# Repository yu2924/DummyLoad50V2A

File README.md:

# Dummy Load 50V2A

ハードウェアプロジェクト**Dummy Load 50V2A**のデザインについてまとめます。

## 1. 概要

**Dummy Load 50V2A**は電源回路の負荷テストなどに便利な、定電流電子負荷装置です。
AVRマイコンを使用して電圧・電流・温度をモニタします。

* 最大定格DC50V、2A、50W程度
* 電圧モニタ分解能: 0.1V
* 電流モニタ分解能: 1mA
* 温度モニタ分解能: 1℃
* 電源: DC9～12V 100mA程度
* 動作中の電圧・電流・温度をモニタしながら、負荷電流をコース・ファインの2つのツマミで設定
* 負荷のON/OFFスイッチ

## 2. ツールとマテリアル

**ソフトウェアツール**
* 回路作図: [BSch3V](https://www.suigyodo.com/online/schsoft.htm) 0.83.05
* PCB設計: [KiCad](https://www.kicad.org/) 5.1
* ファームウェア開発: Atmel Studio 7 ([Microchip Studio 7](https://www.microchip.com/en-us/tools-resources/develop/microchip-studio))
* I2Cライブラリ: USI_TWI_Master ([TinyWireM](https://github.com/adafruit/TinyWireM))
* その他作図: [Inkscape](https://inkscape.org/) 1.1

**ハードウェアツール**
* AVRプログラマ: Atmel AVRISP mkIIまたは同等品
* 電圧計・電流計: 電圧と電流の読み取り値の比較基準に信頼できるものが必要です。とりあえず3 1/2桁のDMMでOKです。

**その他**
* ハンダとハンダゴテ、ニッパーとラジオペンチ、ヤスリ、タップとタップハンドル、等々
* スペーサー、ネジ、ワッシャー、アルミ板、等々

**※AVR開発環境のアップデート**
2022-05-31現在、AVRISP mkIIが既にディスコンということもあり、[MPLAB X IDE](https://www.microchip.com/en-us/tools-resources/develop/mplab-x-ide)と[MPLAB SNAP](https://www.microchip.com/en-us/development-tool/PG164100)への移行が良さそうです。Atmel Studioと同じ[Atmel AVR GNU Toolchain](https://www.microchip.com/en-us/tools-resources/develop/microchip-studio/gcc-compilers)も利用できるようです。

## 3. 回路の略解

[回路図](media/DummyLoad50V2A.pdf)

部品は概ね[秋月電子通商](https://akizukidenshi.com/)で購入できるものを中心に選んでいます。

**電子負荷**
オペアンプとMOSFETを使った電流シンクです。
オペアンプは単電源動作で0V入力できるものから広く選べますが、低オフセットのものが望ましいです。
MOSFETも特定の型番に限らず、定格電圧・電流、許容損失、熱抵抗、Vth(on)などの条件に見合ったものの中から広く選べると思います。

コース・ファインの2つのツマミで制御電圧を合成し、負荷電流を設定します。
回路図中480k～∞としている抵抗はオペアンプのオフセットを相殺するためのオプションであり、設定電流を0mAまで絞り込めない場合に追加します。

:bulb:このデザインは定電流負荷ですが、別のアイデアとして基準電圧をターゲット端子から取れば負荷電流が電圧に比例するオーム負荷となります。

**モニタ**
0～50Vの範囲を0.1Vの分解能で表示、オフセット調節を省略可、という条件で部品を選定しました。

* [AVR ATtiny85](https://www.microchip.com/en-us/product/ATtiny85)
* [外付け16bit 2ch ADC MCP3426](https://www.microchip.com/en-us/product/MCP3426)
* [温度センサ MCP9700A](https://www.microchip.com/en-us/product/MCP9700A)
* [LCDモジュール AQM1602Y-FLW-FBW](https://akizukidenshi.com/catalog/g/gP-12619/)

外付けADCを電圧・電流に、内蔵ADCを温度センサにそれぞれ割り当てます。  
AVRマイコンをLCDモジュールの真下に配置するために実装高さを抑え、[丸ピンＩＣソケット RI-01S-SG/4.2SMT](https://akizukidenshi.com/catalog/g/gP-12368/)を基板に埋め込むように実装します。

**ファームウェア**
内蔵のUSIユニットをI2C動作させるために、TinyWireMライブラリに同梱のUSI_TWI_Masterを利用します。TinyWireMはArduinoのライブラリですが、USI_TWI_MasterはArduinoに依存しません。

**放熱**
ヒートシンクの選択は厳密な熱設計に基づくものではありません。市販の電子負荷装置の中で定格50～100W程度のものに注目し、ワット当たりに必要なサイズを大雑把に見積もったものです。
Amazonで購入した詳細不明なアルミ製ヒートシンクと5cm角の12V DCファンを使用して、強制空冷としています。DCファンは3Dプリンタ向けの製品のようでした。

## 4. 組み立て

[ケガキ図](drawings/draft.svg)

ベースには50×100mm、t=1.0のアルミ板を使用しています。

1. パワーMOSFET以外の部品を基板に実装する。
2. 50mm角のヒートシンクにはM3タップを立て、10mm角の垂直取付用ブロックを使って基板と繋ぐ。
3. パワーMOSFETをヒートシンクに取り付け、基板にはんだ付けする。
4. 50×100mmのアルミ板ベースの上に5mmスペーサーを併用して基板とヒートシンクを固定する。
5. ヒートシンクにファンをテープで固定し、基板へコネクタを繋ぐ。
6. AVRマイコンとLCDを順にソケットに挿し込む。
7. AVRライタをISPピンヘッダに接続し、電源を接続してファームウェアを書き込む。
8. 適当な電圧・電流源を接続し、信頼できる電圧・電流計と表示値が一致するように多回転トリマをそれぞれ調節する。

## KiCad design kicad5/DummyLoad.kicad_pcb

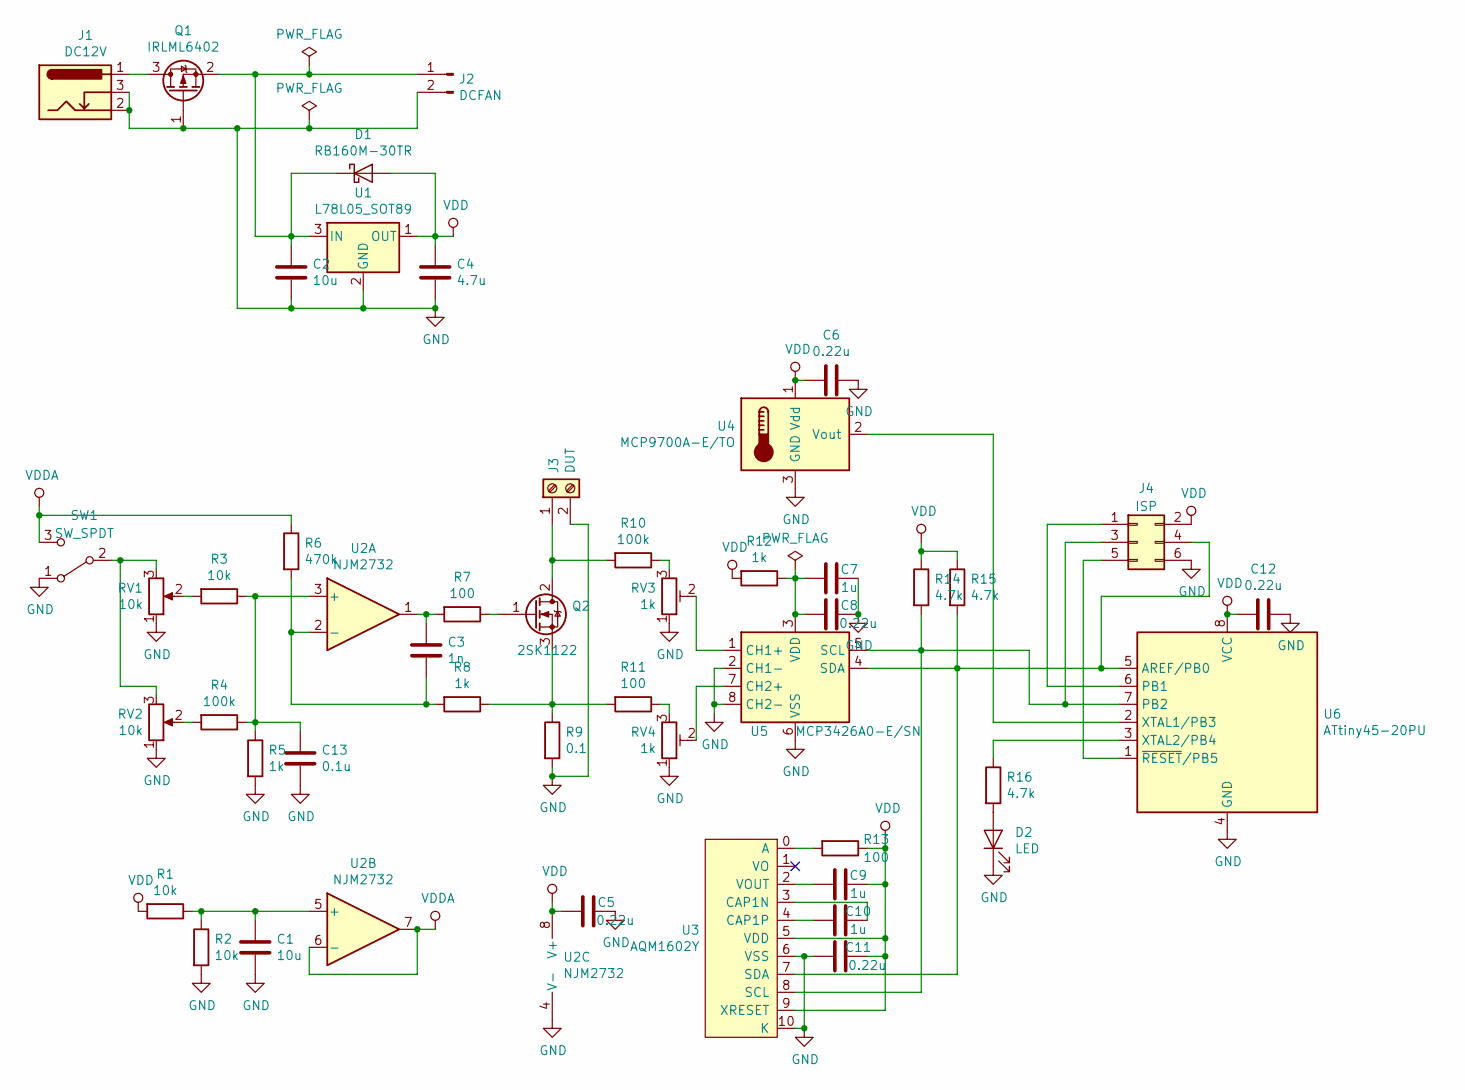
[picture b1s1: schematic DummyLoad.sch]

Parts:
C1: 10u; C_Disc_D4.7mm_W2.5mm_P5.00mm
C2: 10u; C_1206_3216Metric_Pad1.42x1.75mm_HandSolder
C3: 1n; C_Disc_D4.3mm_W1.9mm_P5.00mm
C4: 4.7u; C_0805_2012Metric_Pad1.15x1.40mm_HandSolder
C5, C6, C8, C11, C12: 0.22u; C_0603_1608Metric_Pad1.05x0.95mm_HandSolder
C7, C9, C10: 1u; C_0603_1608Metric_Pad1.05x0.95mm_HandSolder
C13: 0.1u; C_Disc_D4.3mm_W1.9mm_P5.00mm
D1: RB160M-30TR; D_SOD-123
D2: LED; LED_D3.0mm_Horizontal_O3.81mm_Z2.0mm
J1: DC12V; BarrelJack_Horizontal
J2: DCFAN; JST_XH_B2B-XH-A_1x02_P2.50mm_Vertical
J3: DUT; Terminal-2P
J4: ISP; PinHeader_2x03_P2.54mm_Vertical
Q1: IRLML6402; SOT-23
Q2: 2SK1122; TO-3P-3_Vertical
R1, R2, R3: 10k; R_Axial_DIN0204_L3.6mm_D1.6mm_P5.08mm_Horizontal
R4, R10: 100k; R_Axial_DIN0204_L3.6mm_D1.6mm_P5.08mm_Horizontal
R5, R8, R12: 1k; R_Axial_DIN0204_L3.6mm_D1.6mm_P5.08mm_Horizontal
R6: 470k; R_Axial_DIN0204_L3.6mm_D1.6mm_P5.08mm_Horizontal
R7, R11, R13: 100; R_Axial_DIN0204_L3.6mm_D1.6mm_P5.08mm_Horizontal
R9: 0.1; R_Box_L13.0mm_W4.0mm_P9.00mm
R14, R15, R16: 4.7k; R_Axial_DIN0204_L3.6mm_D1.6mm_P5.08mm_Horizontal
RV1, RV2: 10k; Potentiometer_Alps_RK09K_Single_Vertical
RV3, RV4: 1k; Potentiometer_Bourns_3296W_Vertical
SW1: SW_SPDT; SPDT-PCB
U1: L78L05_SOT89; SOT-89-3
U2: NJM2732; DIP-8_W7.62mm
U3: AQM1602Y
U4: MCP9700A-E/TO; TO-92_Inline_Wide
U5: MCP3426A0-E/SN; SOIC-8_3.9x4.9mm_P1.27mm
U6: ATtiny45-20PU; DIP-8_W7.62mm-LoProf

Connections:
GND: C1.2, C2.2, C4.2, C5.2, C6.2, C7.2, C8.2, C11.2, C12.2, C13.2, D2.1 (K), J1.2, J1.3, J2.2, J3.2, J4.6, Q1.1 (G), R2.2, R5.2, R9.2, RV1.0, RV1.1, RV2.0, RV2.1, RV3.1, RV4.1, SW1.1 (A), U1.2 (GND), U2.4 (V-), U3.6 (VSS), U3.10 (K), U4.3 (GND), U5.2 (CH1-), U5.6 (VSS), U5.8 (CH2-), U6.4 (GND)
unnamed: C1.1, R1.1, R2.1, U2.5 (+)
unnamed: C2.1, D1.1 (K), J2.1, Q1.2 (S), U1.3 (IN)
unnamed: C3.1, R7.2, U2.1
unnamed: C3.2, R6.2, R8.2, U2.2 (-)
unnamed: C7.1, C8.1, R12.1, U5.3 (VDD)
unnamed: C9.2, U3.2 (VOUT)
unnamed: C10.1, U3.3 (CAP1N)
unnamed: C10.2, U3.4 (CAP1P)
unnamed: C13.1, R3.1, R4.1, R5.1, U2.3 (+)
unnamed: D2.2 (A), R16.2
unnamed: J1.1, Q1.3 (D)
unnamed: J3.1, Q2.2 (D), R10.2
unnamed: J4.1, U6.6 (PB1)
unnamed: J4.3, R14.2, U3.8 (SCL), U5.5 (SCL), U6.7 (PB2)
unnamed: J4.4, R15.2, U3.7 (SDA), U5.4 (SDA), U6.5 (AREF/PB0)
unnamed: J4.5, U6.1 (~RESET~/PB5)
unnamed: Q2.1 (G), R7.1
unnamed: Q2.3 (S), R8.1, R9.1, R11.2
unnamed: R3.2, RV1.2
unnamed: R4.2, RV2.2
unnamed: R10.1, RV3.3
unnamed: R11.1, RV4.3
unnamed: R13.2, U3.0 (A)
unnamed: R16.1, U6.3 (XTAL2/PB4)
unnamed: RV1.3, RV2.3, SW1.2 (B)
unnamed: RV3.2, U5.1 (CH1+)
unnamed: RV4.2, U5.7 (CH2+)
unnamed: U4.2 (Vout), U6.2 (XTAL1/PB3)
VDD: C4.1, C5.1, C6.1, C9.1, C11.1, C12.1, D1.2 (A), J4.2, R1.2, R12.2, R13.1, R14.1, R15.1, U1.1 (OUT), U2.8 (V+), U3.5 (VDD), U3.9 (XRESET), U4.1 (Vdd), U6.8 (VCC)
VDDA: R6.1, SW1.3 (C), U2.6 (-), U2.7

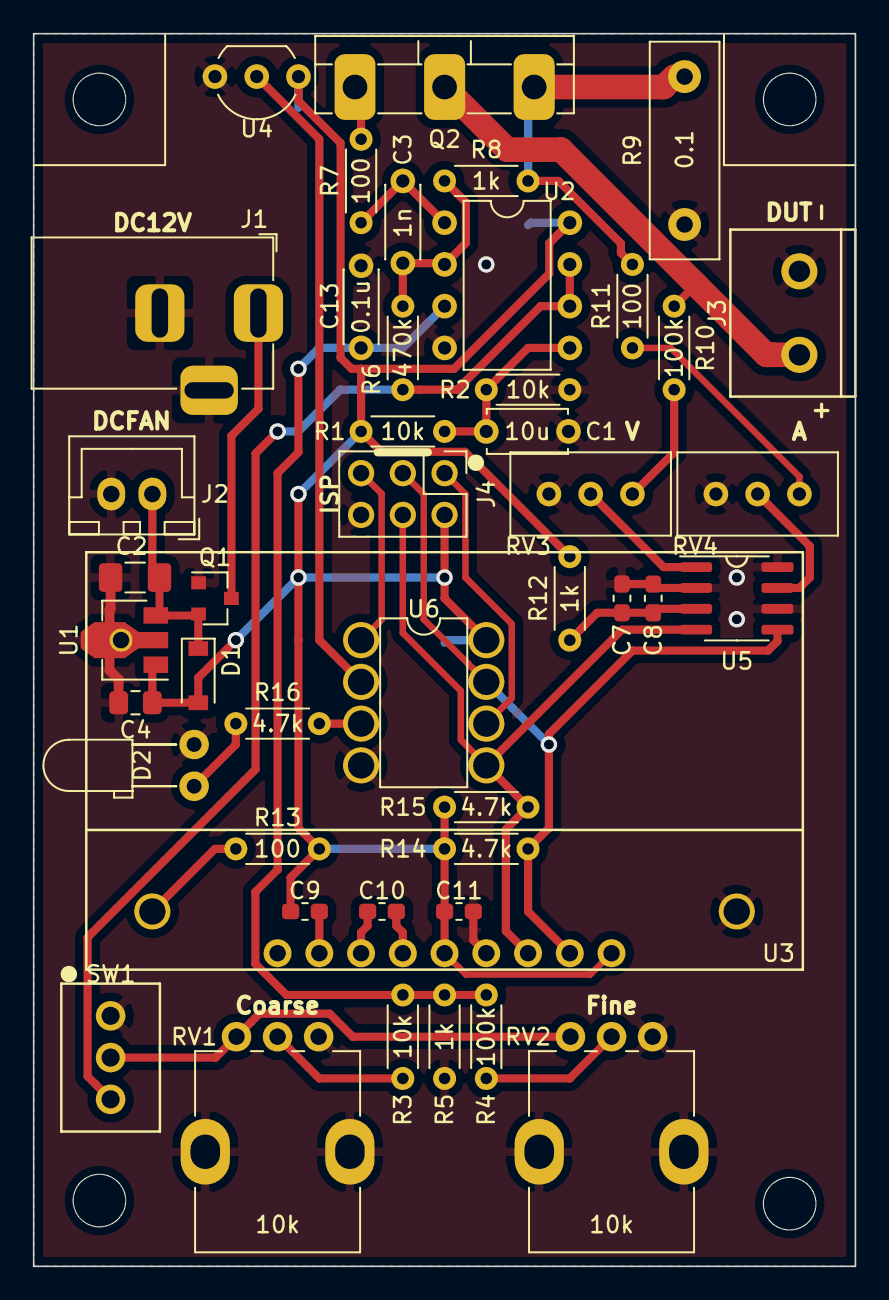
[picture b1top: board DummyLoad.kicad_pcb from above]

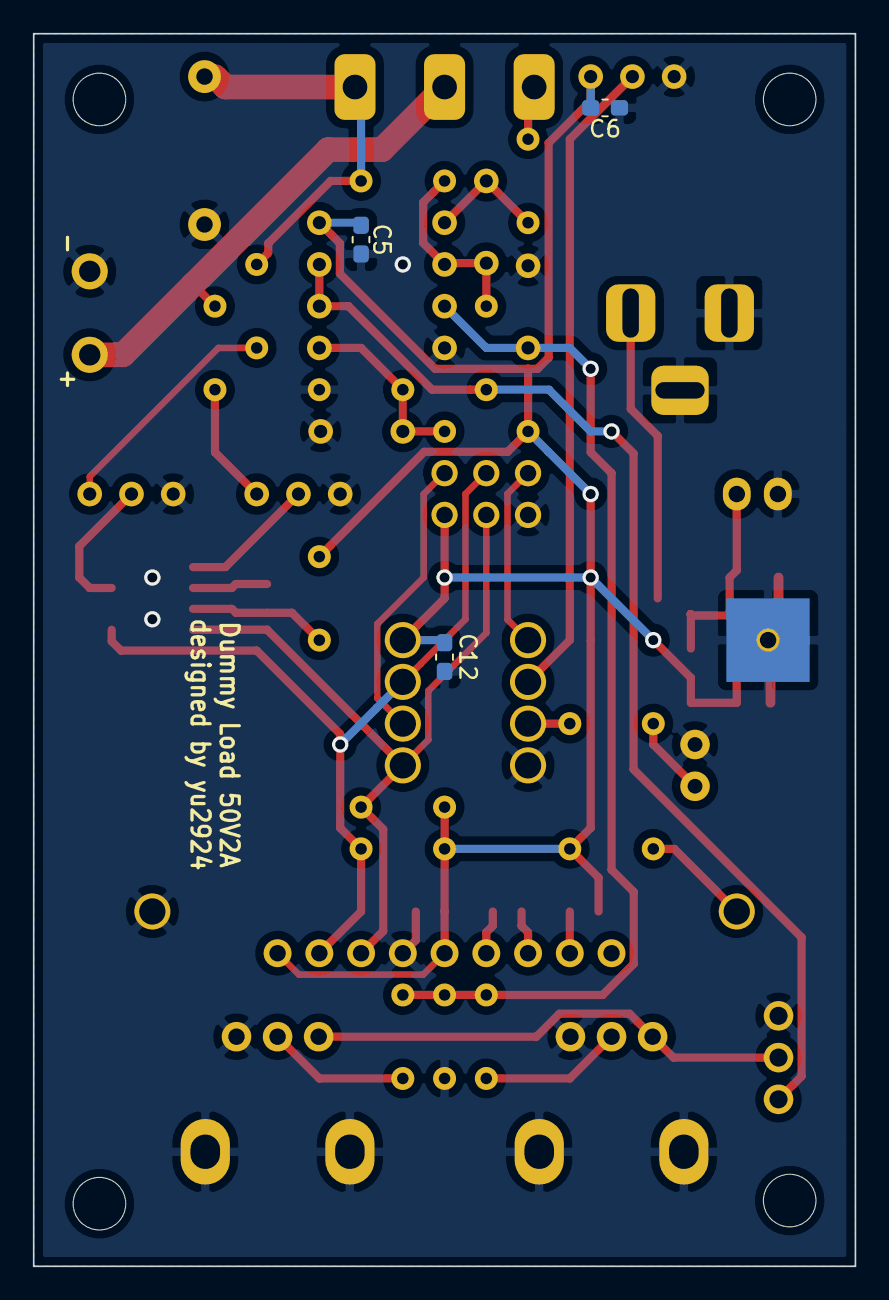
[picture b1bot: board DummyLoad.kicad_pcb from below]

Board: 2 copper layers, 50.0 x 75.0 mm, 48 parts (3 on the bottom side), 31 nets.

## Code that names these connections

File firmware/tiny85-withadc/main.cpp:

/*
 * tiny85-withadc.cpp
 *
 * Created: 2019/08/12 0:39:17
 * Author : yu2924
 */ 

#include <avr/io.h>
#include <avr/interrupt.h>
#include <avr/sleep.h>
#include <util/delay.h>
// to use float with printf, requires linker options: -Wl,-u,vfprintf -lprintf_flt -lm
#include <stdio.h>
#include "USI_TWI_Master.h"
#include "MCP342x.h"
#include "ST7032i.h"

inline uint8_t getbit(volatile uint8_t& port, uint8_t bit) {return (port >> bit) & 0x01;}
inline void setbit(volatile uint8_t& port, uint8_t bit, uint8_t v) {port = (port & (uint8_t)~(1 << bit)) | (v << bit);}
	
inline int roundd2ip(double v) { return (int)(v + 0.5); }
inline int16_t absi16(int16_t v) { return (0 <= v) ? v : -v; }

struct AverageBuffer8ui
{
	uint16_t totalsum;
	uint8_t buffer[4];
	uint8_t pos;
	uint8_t push(uint8_t vnew)
	{
		uint8_t vlast = buffer[pos & 0x03];
		totalsum -= vlast;
		buffer[pos & 0x03] = vnew;
		totalsum += vnew;
		pos ++;
		return (uint8_t)(totalsum >> 2);
	}
};

struct AverageBuffer14i
{
	int16_t totalsum;
	int16_t buffer[4];
	uint8_t pos;
	int16_t push(int16_t vnew)
	{
		int16_t vlast = buffer[pos & 0x03];
		totalsum -= vlast;
		buffer[pos & 0x03] = vnew;
		totalsum += vnew;
		pos ++;
		return totalsum >> 2;
	}
};

#define LED_PORT PORTB
#define LED_BIT PB4

static const uint8_t CG_CDEG[] =
{
	0b00001000,
	0b00010110,
	0b00001001,
	0b00001000,
	0b00001000,
	0b00001001,
	0b00000110,
	0b00000000,
};

int main(void)
{
	// clock prescaler
	CLKPR = (1<<CLKPCE); // enable change
	CLKPR = (0b0000<<CLKPS0); // divisor=1 (8MHz)
	// PortB
	DDRB = (1<<DDB4); // LED output: PB4
	PORTB = (1<<PB5)|(1<<PB1); // pull-up enabled: unused pins PB1, PB5
	// ADC
	ADMUX = (0<<REFS0)|(1<<ADLAR)|(0<<REFS2)|(0b0011<<MUX0); // vref=Vcc, alignment=left-justified, mux=ADC3(PB3)
	ADCSRA = (1<<ADEN)|(0<<ADATE)|(0<<ADIF)|(0<<ADIE)|(0b110<<ADPS0); // ADC=enabled, auto-trigger=disabled, interrupt=disabled, prescaler=1/64 (125kHz)
	ADCSRB = (0<<BIN)|(0<<IPR)|(0b000<<ADTS0); // bipolar=no, polarity-reversal=no, triggersource=freerunning
	DIDR0 = (1<<ADC3D); // digital-input-disabled-ADC3(PB3)=yes
	// timer1
	TCCR1 = (1<<CTC1)|(0b1111<<CS10); // enable CTC, divisor=16384 (488.3Hz)
	GTCCR = 0;
	OCR1A = 24; // tick = 20.35Hz (fire interrupt)
	OCR1C = 24; // tick = 20.35Hz (reset counter)
	TIMSK = (1<<OCIE1A); // enable interrupt
	PLLCSR = 0; // no PLL
	// i2c
	USI_TWI_Master_Initialise();
	MCP342x mcp3426 = {};
	ST7032i st7032i = {};
	mcp3426.initialize(MCP342X_I2CADDR);
	st7032i.initialize(ST7032_I2CADDR, 0, 35); // AQM1602XA or AQM1602Y, 5V
	st7032i.writeCommand(ST7032CmdSetDDRAMAddr | ST7032DDRAMOffsetL1);
	st7032i.writeString("Dummy Load 50V2A");
	st7032i.writeCommand(ST7032CmdSetDDRAMAddr | ST7032DDRAMOffsetL2);
	st7032i.writeString("by yu2924");
	st7032i.writeCommand(ST7032CmdSetCGRAMAddr | 8); // for char_code='\x1', char_height=8
	st7032i.writeData(CG_CDEG, sizeof(CG_CDEG));
	for(int i = 0; i < 2; i ++)
	{
		_delay_ms(500);
		setbit(LED_PORT, LED_BIT, 1);
		_delay_ms(500);
		setbit(LED_PORT, LED_BIT, 0);
	}
	st7032i.writeCommand(ST7032CmdClearDisplay);
	// run
	// T:
	//   MCP9700A: Vmeas=0.5+T/100 => Tmeas=(Vmeas-0.5)*100
	//   ADC: Vmeas/5=vcode/255 => Vmeas=5*vcode/255=vcode/51, vcode=255*Vmeas/5=Vmeas*51
	//   Tmeas=(vcode/51-0.5)*100
	//   vcode=(0.5+Tmeas/100)*51
	// V:
	//   Vfs=0.25V
	//   ADC: Vmeas/50=vcode/8191
	//   Vmeas=50*vcode/8191=vcode/163.82
	//   vcode=8191*Vmeas/50=Vmeas*163.82
	//
	// I:
	//   Vfs=0.15V
	//   ADC: Imeas/1.2=vcode/(8191*0.15/0.25)=vcode/4914.6
	//   Imeas=1.2*vcode/4914.6=vcode/4095.5
	//   vcode=4914.6*Imeas/1.2=Imeas*4095.5
	static const int Tht = 60;
	static const double Av = 1.0 / 163.82;
	static const double Ai = 1000.0 / 2800.0; // 4095.5;
	AverageBuffer8ui averaget = {};
	AverageBuffer14i averagev = {};
	AverageBuffer14i averagei = {};
	char str[16];
	bool flipch = false;
	ADCSRA |= (1<<ADSC); // trigger internal ADC
	mcp3426.StartConversion(MCP342X_CH1 | MCP342X_ONESHOT | MCP342X_SIZE_14 | MCP342X_PGA_X8);
	sei();
	set_sleep_mode(SLEEP_MODE_IDLE);
	sleep_mode();
	while(1)
	{
		uint8_t vt = averaget.push(ADCH);
		int tmeas = roundd2ip(((double)vt / 51.0 - 0.5) * 100.0);
		sprintf(str, "T:%d\x1 ", tmeas);
		st7032i.writeCommand(ST7032CmdSetDDRAMAddr | (ST7032DDRAMOffsetL1 + 10));
		st7032i.writeString(str);
		setbit(LED_PORT, LED_BIT, (Tht <= tmeas) ? 1 : 0);
		ADCSRA |= (1<<ADSC); // trigger internal ADC
		if(!flipch)
		{
			int16_t v; uint8_t cfg; mcp3426.GetResult14(&v, &cfg);
			v = averagev.push(absi16(v));
			sprintf(str, "V:%4.1fV ", (double)v * Av);
			// sprintf(str, "V:%4.1fV %d ", (double)v * Av, v);
			st7032i.writeCommand(ST7032CmdSetDDRAMAddr | ST7032DDRAMOffsetL1);
			st7032i.writeString(str);
			mcp3426.StartConversion(MCP342X_CH2 | MCP342X_ONESHOT | MCP342X_SIZE_14 | MCP342X_PGA_X8);
		}
		else
		{
			int16_t v; uint8_t cfg; mcp3426.GetResult14(&v, &cfg);
			v = averagei.push(absi16(v));
			sprintf(str, "I:%2dmA ", roundd2ip((double)v * Ai));
			// sprintf(str, "I:%2dmA %d ", roundd2ip((double)v * Ai), v);
			st7032i.writeCommand(ST7032CmdSetDDRAMAddr | ST7032DDRAMOffsetL2);
			st7032i.writeString(str);
			mcp3426.StartConversion(MCP342X_CH1 | MCP342X_ONESHOT | MCP342X_SIZE_14 | MCP342X_PGA_X8);
		}
		flipch = !flipch;
		sleep_mode();
	}
	return 0;
}

ISR(TIM1_COMPA_vect)
{
}

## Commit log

2022-07-17 Create LICENSE
